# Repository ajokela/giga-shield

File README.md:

# Arduino Giga R1 WiFi Shield - Driven Level Shifter Redesign

## Overview

This is a redesigned shield/daughter board for the **Arduino Giga R1 WiFi** that replaces the original TXB0108PW auto-sensing bidirectional level translators with **SN74LVC8T245PW** driven (direction-controlled) level shifters.

The board provides 72 channels of 3.3V-to-5V level shifting across 9 ICs, mapping the Giga's 3.3V GPIO signals to 5V-compatible headers suitable for interfacing with retro hardware such as the Z80 CPU via a RetroShield.

## Why the Redesign

The original board used **TXB0108PW** auto-sensing bidirectional level translators. While convenient (no direction pin needed), the auto-sensing mechanism fails during Z80 bus cycles when signals are tri-stated. During these periods, the TXB0108 cannot determine the correct drive direction, causing the Arduino to be completely blind to certain Z80 execution states. This makes reliable bus monitoring and intervention impossible.

The **SN74LVC8T245PW** is a driven (explicit direction control) 8-bit dual-supply bus transceiver. The DIR pin explicitly sets the translation direction:
- **DIR LOW** = A-port to B-port (3.3V to 5V)
- **DIR HIGH** = B-port to A-port (5V to 3.3V)

This eliminates the ambiguity during tri-state periods and gives the Arduino full control over when it's reading vs. writing the bus.

## Board Specifications

| Parameter | Value |
|-----------|-------|
| Dimensions | 155mm x 90mm |
| Layers | 2 (top + bottom copper) |
| Level Shifters | 9x SN74LVC8T245PW (TSSOP-24) |
| Decoupling Caps | 27x 0.1uF ceramic (0603) |
| DIR Pull-downs | 9x 10K resistor (0603) |
| Connectors | 10x pin headers (J1-J10) + 1x DIR control (J11) |
| Mounting Holes | 4x 3.2mm |
| Traces | 1843 |
| Vias | 158 |

## Signal Mapping

Each SN74LVC8T245PW translates 8 signals between the Giga's 3.3V domain (A-port) and the 5V headers (B-port).

### U1 - SCL/SDA/D9-D13
| A-Port (3.3V) | B-Port (5V) | Function |
|----------------|-------------|----------|
| SCL1 | PB6 | I2C Clock |
| SDA1 | PH12 | I2C Data |
| AREF_3V3 | AREF | Analog Reference |
| D13 | PH6 | Digital 13 |
| D12 | PJ11 | Digital 12 |
| D11 | PJ10 | Digital 11 |
| D10 | PK1 | Digital 10 |
| D9 | PB9 | Digital 9 |

### U2 - Analog A0-A7
| A-Port (3.3V) | B-Port (5V) | Function |
|----------------|-------------|----------|
| PC4 | A0 | Analog 0 |
| PC5 | A1 | Analog 1 |
| PB0 | A2 | Analog 2 |
| PB1 | A3 | Analog 3 |
| PC3 | A4 | Analog 4 |
| PC2 | A5 | Analog 5 |
| PC0 | A6 | Analog 6 |
| PA0 | A7 | Analog 7 |

### U3 - Digital D1-D8
| A-Port (3.3V) | B-Port (5V) | Function |
|----------------|-------------|----------|
| D8 | PB8 | Digital 8 |
| D7 | PB4 | Digital 7 |
| D6 | PD13_5V | Digital 6 |
| D5 | PA7 | Digital 5 |
| D4 | PJ8 | Digital 4 |
| D3 | PA2 | Digital 3 |
| D2 | PA3 | Digital 2 |
| D1 | PA9 | Digital 1 |

### U4 - Analog A8-A11, DAC, CAN
| A-Port (3.3V) | B-Port (5V) | Function |
|----------------|-------------|----------|
| PC2_C | A8 | Analog 8 |
| PC3_C | A9 | Analog 9 |
| PA1_C | A10 | Analog 10 |
| PA0_C | A11 | Analog 11 |
| PA4 | DAC0 | DAC Channel 0 |
| PA5 | DAC1 | DAC Channel 1 |
| PB5 | CAN_RX | CAN Bus RX |
| PB13 | CAN_TX | CAN Bus TX |

### U5 - Digital D0, D14-D20
| A-Port (3.3V) | B-Port (5V) | Function |
|----------------|-------------|----------|
| D0 | PB7 | Digital 0 |
| D14 | PG14 | Digital 14 |
| D15 | PC7 | Digital 15 |
| D16 | PH13 | Digital 16 |
| D17 | PI9 | Digital 17 |
| D18 | PD5 | Digital 18 |
| D19 | PD6 | Digital 19 |
| D20 | PB11 | Digital 20 |

### U6 - Digital Even D22-D36
| A-Port (3.3V) | B-Port (5V) | Function |
|----------------|-------------|----------|
| D22 | PJ12 | Digital 22 |
| D24 | PG12 | Digital 24 |
| D26 | PJ14 | Digital 26 |
| D28 | PJ15 | Digital 28 |
| D30 | PK3 | Digital 30 |
| D32 | PK4 | Digital 32 |
| D34 | PK5 | Digital 34 |
| D36 | PK6 | Digital 36 |

### U7 - Digital Odd D37-D51
| A-Port (3.3V) | B-Port (5V) | Function |
|----------------|-------------|----------|
| D37 | PJ6 | Digital 37 |
| D39 | PI14 | Digital 39 |
| D41 | PK7 | Digital 41 |
| D43 | PI10 | Digital 43 |
| D45 | PI13 | Digital 45 |
| D47 | PB2 | Digital 47 |
| D49 | PE4 | Digital 49 |
| D51 | PE5 | Digital 51 |

### U8 - Digital Odd D21-D35
| A-Port (3.3V) | B-Port (5V) | Function |
|----------------|-------------|----------|
| D21 | PH4 | Digital 21 |
| D23 | PG13 | Digital 23 |
| D25 | PJ0 | Digital 25 |
| D27 | PJ1 | Digital 27 |
| D29 | PJ2 | Digital 29 |
| D31 | PJ3 | Digital 31 |
| D33 | PJ4 | Digital 33 |
| D35 | PJ5 | Digital 35 |

### U9 - Digital Even D38-D52
| A-Port (3.3V) | B-Port (5V) | Function |
|----------------|-------------|----------|
| D38 | PJ7 | Digital 38 |
| D40 | PE6 | Digital 40 |
| D42 | PI15 | Digital 42 |
| D44 | PG10 | Digital 44 |
| D46 | PH15 | Digital 46 |
| D48 | PK0 | Digital 48 |
| D50 | PI11 | Digital 50 |
| D52 | PK2 | Digital 52 |

## DIR Control (J11)

The J11 header provides per-shifter direction control. Each pin corresponds to one SN74LVC8T245PW's DIR input. A **10K pull-down resistor** on each DIR line defaults the direction to **A-to-B (3.3V to 5V)**.

| J11 Pin | Signal | Controls |
|---------|--------|----------|
| 1 | DIR_U1 | U1 (SCL/SDA/D9-D13) |
| 2 | DIR_U2 | U2 (A0-A7) |
| 3 | DIR_U3 | U3 (D1-D8) |
| 4 | DIR_U4 | U4 (A8-A11/DAC/CAN) |
| 5 | DIR_U5 | U5 (D0/D14-D20) |
| 6 | DIR_U6 | U6 (Even D22-D36) |
| 7 | DIR_U7 | U7 (Odd D37-D51) |
| 8 | DIR_U8 | U8 (Odd D21-D35) |
| 9 | DIR_U9 | U9 (Even D38-D52) |
| 10 | GND | Ground reference |

To change a shifter's direction to **B-to-A (5V to 3.3V)**, drive the corresponding J11 pin HIGH (3.3V). This is done by running jumper wires from available Giga GPIO pins to the J11 header. Software then controls direction by toggling those GPIOs.

## Connectors

| Ref | Type | Pins | Location | Function |
|-----|------|------|----------|----------|
| J1 | 1x8 | 8 | Bottom edge | Giga 3.3V analog header |
| J2 | 1x10 | 10 | Top edge | Giga 3.3V header (power/analog ext) |
| J3 | 1x8 | 8 | Bottom edge | Giga 3.3V digital D1-D8 |
| J4 | 1x8 | 8 | Top edge | Giga 3.3V digital SCL/SDA/D9-D13 |
| J5 | 1x26 | 26 | Bottom edge | 5V analog header (J_ANALOG) |
| J6 | 1x8 | 8 | Bottom edge | Giga 3.3V digital D0/D14-D20 |
| J7 | 1x8 | 8 | Top edge | Giga 3.3V D21 + misc |
| J8 | 1x26 | 26 | Top edge | 5V digital header (J_DIGITAL) |
| J9 | 2x18 | 36 | Right side | 3.3V side connector (JSIDE) |
| J10 | 2x18 | 36 | Right side | 5V side connector (JSIDE_5V) |
| J11 | 1x10 | 10 | Center-left | DIR control header |

## Design Toolchain

The original board was designed in **KiCad 9.0** (file version 20241229). Since pcb-rnd 3.1.4 cannot read KiCad 9.0 files (version too new), the board was rebuilt from scratch using a Python generator script.

### Tools Used

| Tool | Version | Purpose |
|------|---------|---------|
| KiCad | 9.0.6 | Original design source, position/netlist reference |
| pcb-rnd | 3.1.4 | PCB format, DSN export, gerber/PNG export |
| Freerouting | 1.9.0 | Specctra-based autorouter |
| Python | 3.x | Board generator script (`build_giga_shield.py`) |

### Build Pipeline

1. **`build_giga_shield.py`** generates `giga_shield.pcb` with all components placed, footprints defined, and netlist specified in pcb-rnd native format
2. **pcb-rnd** exports the unrouted board to Specctra DSN format (`giga_shield.dsn`)
3. **Freerouting** reads the DSN, autoroutes all nets, and outputs a Specctra session file (`giga_shield.ses`)
4. **`ses_to_pcb.py`** imports the routed traces from the SES file back into the PCB
5. **pcb-rnd** exports final gerbers, drill files, and photo-realistic PNG renderings

### Key Implementation Details

- Component positions were extracted from the original KiCad PCB and translated from KiCad's coordinate origin (x=106mm, y=30.5mm) to pcb-rnd's (0,0) origin using the `kpos()` function
- All 1x pin headers are rotated 90 degrees to run horizontally along the board edges, matching the original KiCad layout (the Arduino Giga shield form factor has edge-parallel headers)
- TSSOP-24 footprints are generated programmatically with correct 0.65mm pitch, 6.4mm pad-to-pad span
- The SN74LVC8T245PW pin mapping was carefully verified against the datasheet: pins 1-12 on the left (DIR, A1-A4, GND, A5-A8, OE#, GND) and pins 13-24 on the right (B8-B5, VCCB, B4-B1, VCCA, VCCA, VCCB)
- OE# (pin 11) is tied to GND on all shifters (always enabled)
- Each shifter has two 0.1uF decoupling caps: one on VCCA (3.3V) and one on VCCB (5V)
- An additional 9 decoupling caps are placed along the bottom edge for power rail filtering

## SN74LVC8T245PW vs TXB0108PW

| Feature | TXB0108PW (Original) | SN74LVC8T245PW (New) |
|---------|----------------------|----------------------|
| Package | TSSOP-20 | TSSOP-24 |
| Channels | 8 | 8 |
| Direction | Auto-sensing | Explicit DIR pin |
| A-Port Voltage | 1.2V - 3.6V | 1.2V - 3.6V |
| B-Port Voltage | 1.65V - 5.5V | 1.65V - 5.5V |
| Max Data Rate | 100 Mbps | 380 Mbps |
| Tri-state Handling | Unreliable | Deterministic |
| Output Enable | OE (active low) | OE# (active low) |
| Extra Pins | None | DIR control |

## Files

| File | Description |
|------|-------------|
| `build_giga_shield.py` | Python script that generates the entire PCB from scratch |
| `giga_shield.pcb` | Final routed PCB in pcb-rnd format |
| `giga_shield.dsn` | Specctra DSN export for autorouting |
| `giga_shield.ses` | Specctra session file with routing solution |
| `giga_shield_bom.csv` | Bill of materials |
| `giga_shield_centroid.csv` | Pick-and-place centroid file (SMD components) |
| `giga_shield_gerbers.zip` | Production files (gerbers + BOM + centroid) |
| `giga_shield_top.png` | Photo-realistic top view rendering |
| `giga_shield_bottom.png` | Photo-realistic bottom view rendering |
| `sn74lvc8t245_pinout.txt` | SN74LVC8T245 pinout reference |
| `kicad_source/` | Original KiCad 9.0 design files (reference) |
| `kicad_source/AlexJ_bz_ArduinoGigaShield.kicad_pcb` | Original KiCad PCB |
| `kicad_source/AlexJ_bz_ArduinoGigaShield.kicad_sch` | Original KiCad schematic |
| `kicad_source/AlexJ_bz_ArduinoGigaShield.pdf` | Original schematic PDF |
| `kicad_source/giga_pos.csv` | Component positions exported from KiCad |
| `kicad_source/giga_netlist.d356` | IPC-D-356 netlist exported from KiCad |

## Board Renderings

### Top

### Bottom

## Development Notes

This section documents the full development process, including toolchain issues, format debugging, and workarounds encountered during the redesign.

### Starting Point

The original design (`AlexJ_bz_ArduinoGigaShield.kicad_pcb`) was created in **KiCad 9.0** (internal file version 20241229) with 9x TXB0108PW auto-sensing level shifters. The goal was to convert this to pcb-rnd format, swap in SN74LVC8T245PW driven shifters, and produce a fully routed production board.

### KiCad 9.0 to pcb-rnd Conversion Failure

pcb-rnd 3.1.4 includes an `io_kicad` plugin for reading KiCad files, but it only supports older KiCad versions. Attempting to open the KiCad 9.0 PCB produced:

```
unexpected layout version number (perhaps too new)
```

This was a hard blocker — there is no format converter from KiCad 9.0 to pcb-rnd.

### Extracting Data from KiCad

Since direct conversion was impossible, component positions and netlist data were extracted from KiCad using available tools:

1. **Component positions** were exported using `kicad-cli`:
   ```
   kicad-cli pcb export pos AlexJ_bz_ArduinoGigaShield.kicad_pcb -o giga_pos.csv
   ```

2. **Netlist/connectivity** was exported via IPC-D-356:
   ```
   kicad-cli pcb export ipc2581 ... -o giga_netlist.d356
   ```

3. **Signal mappings** (which Giga pin connects to which 5V header pin through which shifter) were extracted by parsing the KiCad schematic file (`AlexJ_bz_ArduinoGigaShield.kicad_sch`), which uses an s-expression format with positional net connections across hierarchical sheets.

### Building the Board from Scratch

With positions and netlist in hand, `build_giga_shield.py` was written to generate the entire pcb-rnd board programmatically. This script:

- Converts KiCad coordinates to pcb-rnd coordinates (KiCad origin at x=106mm, y=30.5mm; pcb-rnd at 0,0) using:
  ```python
  KX, KY = 106.0, 30.5
  def kpos(kx, ky):
      return (mm(kx - KX), mm(ky - KY))
  ```
- Generates TSSOP-24 footprints for the SN74LVC8T245PW (0.65mm pitch, 6.4mm pad-to-pad span, 24 pins with correct pin naming)
- Creates 0603 SMD footprints for decoupling caps and pull-down resistors
- Creates through-hole pin header footprints with rotation support
- Builds the complete netlist mapping all 72 signal channels across 9 shifters
- Outputs a valid pcb-rnd `.pcb` file

### pcb-rnd Format Debugging

Getting pcb-rnd to accept the generated file required solving several format issues. pcb-rnd's parser error messages were often unhelpful — errors in element definitions would sometimes be reported at a much later line (e.g., the outline layer starting at line 959).

**Issue 1: Element `"smd"` flag**

```
Element["smd" "TSSOP24" "U1" ...]
```
pcb-rnd rejected this with `Unknown flag: smd ignored`, which cascaded into a parse failure. The fix was to use an empty string for the first field:
```
Element["" "TSSOP24" "U1" ...]
```

**Issue 2: Bare `0` without unit suffix**

Mixed use of `0` and `0nm` in coordinate values caused silent parse errors:
```
Pin[0 0 1700000nm ...]    # WRONG - bare 0
Pin[0nm 0nm 1700000nm ...]  # CORRECT
```
All zero values needed the explicit `nm` suffix for consistency.

**Issue 3: Layer `Line[]` missing flags argument**

The `Line[]` entry inside Layer blocks requires 7 fields, but the generator was only outputting 6 (omitting the flags string):
```
Line[x1 y1 x2 y2 thickness clearance]           # WRONG - 6 fields
Line[x1 y1 x2 y2 thickness clearance "clearline"]  # CORRECT - 7 fields
```
The error was `syntax error, unexpected ']', expecting INTEGER or STRING`, which appeared at the outline layer rather than at the actual problematic line.

**Debugging technique: Binary search with file truncation**

Since pcb-rnd always reported the error at the same line regardless of where the actual issue was, a binary search approach was used — progressively truncating the file with `head -N` to isolate which section introduced the parse failure:
```
head -100 giga_shield.pcb > test.pcb && pcb-rnd -x png test.pcb  # OK → mounting holes fine
head -300 giga_shield.pcb > test.pcb && pcb-rnd -x png test.pcb  # OK → connectors fine
head -500 giga_shield.pcb > test.pcb && pcb-rnd -x png test.pcb  # OK → shifters fine
head -700 giga_shield.pcb > test.pcb && pcb-rnd -x png test.pcb  # OK → all elements fine
head -960 giga_shield.pcb > test.pcb && pcb-rnd -x png test.pcb  # FAIL → layers are the problem
```
This narrowed the issue to the Layer blocks, where the missing flags argument was found.

### Connector Rotation

The initial build placed all pin headers with pins extending downward (+Y). For the Arduino Giga shield form factor, the long 1x headers actually run horizontally along the board edges. Without rotation, J5 (1x26 at y=84mm) extended 63.5mm downward to y=148mm — well past the 90mm board edge. J11 (1x10 at y=75mm) similarly extended to y=98mm.

The fix involved:
1. Extracting rotation angles from the original KiCad PCB — all 1x headers had 90° or -90° rotation
2. Adding a `rot` parameter to `pin_header_element()` with a rotation transform:
   ```python
   def rotate(px, py):
       if rot == 90:     # KiCad 90° → pins extend in +X
           return (py, -px)
       elif rot == -90:  # KiCad -90° → pins extend in -X
           return (-py, px)
       return (px, py)
   ```
3. Applying rotation to both pin coordinates and element outlines

After rotation, all connectors fit within the board:
- J5 (1x26): x=[40.6, 104.1], y=84.2 — runs along the bottom edge
- J8 (1x26): x=[39.0, 102.5], y=6.8 — runs along the top edge
- J11 (1x10): x=[40.0, 62.9], y=75.0 — runs horizontally on the board

### Remote Toolchain

pcb-rnd is not readily available on macOS. All pcb-rnd operations (DSN export, gerber generation, PNG rendering) were performed on a remote Linux machine via SSH:

```bash
# Upload PCB
scp giga_shield.pcb alex@192.168.0.219:/tmp/

# Export DSN for autorouting
ssh alex@192.168.0.219 'cd /tmp && pcb-rnd -x dsn giga_shield.pcb'

# Export gerbers
ssh alex@192.168.0.219 'cd /tmp && pcb-rnd -x gerber giga_shield.pcb'

# Render photo-realistic PNG (600 DPI, green solder mask, gold plating)
ssh alex@192.168.0.219 'pcb-rnd -x png --dpi 600 --photo-mode --outfile top.png giga_shield.pcb'
ssh alex@192.168.0.219 'pcb-rnd -x png --dpi 600 --photo-mode --photo-flip-y --outfile bottom.png giga_shield.pcb'

# Download results
scp alex@192.168.0.219:/tmp/giga_shield.*.gbr .
scp alex@192.168.0.219:/tmp/top.png giga_shield_top.png
```

### Autorouting Pipeline

The routing pipeline uses Specctra DSN/SES interchange format as the bridge between pcb-rnd and Freerouting:

```
giga_shield.pcb → [pcb-rnd DSN export] → giga_shield.dsn
                                               ↓
                                    [Freerouting autorouter]
                                         (~55 minutes)
                                               ↓
giga_shield.pcb ← [ses_to_pcb.py]  ← giga_shield.ses
```

**Freerouting** (v1.9.0) is a Java-based Specctra autorouter:
```bash
java -jar freerouting-1.9.0.jar -de giga_shield.dsn -do giga_shield.ses -mp 60
```
The `-mp 60` flag sets 60 optimization passes. A typical run takes ~55 minutes and produces optimized routing with ~1843 traces and ~158 vias.

**`ses_to_pcb.py`** parses the Freerouting SES output and injects `Line[]` entries (traces) and `Via[]` entries into the pcb-rnd PCB file's Layer blocks.

**`strip_traces.py`** removes all routed traces and autorouted vias from a PCB file, leaving only components and netlist — used to prepare for re-routing after component moves. It identifies autorouted vias by their 914400nm pad size (the default from `ses_to_pcb.py`).

Both helper scripts originate from the [dual-z80](https://github.com/ajokela/dual-z80) project.

### Reproduction Steps

To rebuild the board from scratch:

```bash
# 1. Generate the unrouted PCB
python3 build_giga_shield.py giga_shield.pcb

# 2. Export DSN (on a machine with pcb-rnd installed)
pcb-rnd -x dsn giga_shield.pcb

# 3. Run Freerouting (~55 minutes)
java -jar freerouting-1.9.0.jar -de giga_shield.dsn -do giga_shield.ses -mp 60

# 4. Import routes back into PCB
python3 ses_to_pcb.py giga_shield.ses giga_shield.pcb

# 5. Export gerbers
pcb-rnd -x gerber giga_shield.pcb

# 6. Render board images
pcb-rnd -x png --dpi 600 --photo-mode --outfile giga_shield_top.png giga_shield.pcb
pcb-rnd -x png --dpi 600 --photo-mode --photo-flip-y --outfile giga_shield_bottom.png giga_shield.pcb
```

To re-route after component changes:
```bash
# Strip existing traces
python3 strip_traces.py giga_shield.pcb

# Then repeat steps 2-6 above
```

## License

BSD 3-Clause License

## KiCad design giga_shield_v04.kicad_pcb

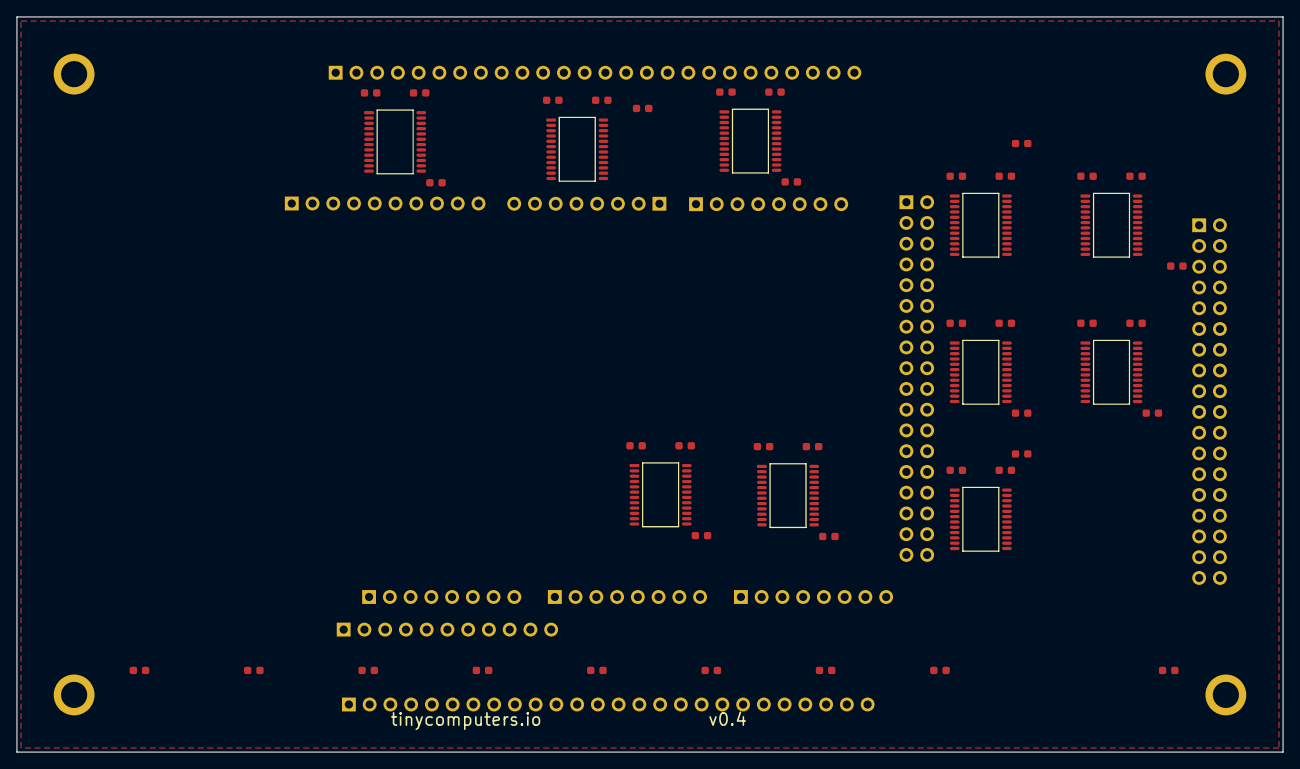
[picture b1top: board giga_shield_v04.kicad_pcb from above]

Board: 2 copper layers, 155.0 x 90.0 mm, 64 parts (0 on the bottom side), 161 nets, no tracks yet.

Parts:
C1, C2, C3, C4, C5, C6, C7, C8, C9, C10, C11, C12, C13, C14, C15, C16, C17, C18, C19, C20, C21, C22, C23, C24, C25, C26, C27, C28, C29: 0.1uF; R_0603_1608Metric
H1, H2, H3, H4: MountingHole; MountingHole_3.2mm_M3
J1, J3, J4, J6, J7: Conn_01x08; Connector_PinHeader_1x08_P2.54mm_Vertical
J2: Conn_01x10; Connector_PinHeader_1x10_P2.54mm_Vertical
J5: J_ANALOG; Connector_PinHeader_1x26_P2.54mm_Vertical
J8: J_DIGITAL; Connector_PinHeader_1x26_P2.54mm_Vertical
J9: JSIDE; Connector_PinHeader_2x18_P2.54mm_Vertical
J10: JSIDE_5V; Connector_PinHeader_2x18_P2.54mm_Vertical
J11: DIR_CTRL; Connector_PinHeader_1x11_P2.54mm_Vertical
R1, R2, R3, R4, R5, R6, R7, R8, R9, R10: 10K; R_0603_1608Metric
U1, U2, U3, U4, U5, U6, U7, U8, U9, U10: SN74LVC8T245PW; TSSOP-24_4.4x7.8mm_P0.65mm

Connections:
+3V3: C1.1, C3.1, C5.1, C7.1, C9.1, C11.1, C13.1, C15.1, C17.1, C19.1, C21.1, C23.1, C25.1, C27.1, C29.1, J2.2, J2.3, J5.4, J7.5, R10.2, U1.22, U1.23, U2.22, U2.23, U3.22, U3.23, U4.22, U4.23, U5.22, U5.23, U6.22, U6.23, U7.22, U7.23, U8.22, U8.23, U9.22, U9.23, U10.22, U10.23
+5V: C2.1, C4.1, C6.1, C8.1, C10.1, C12.1, C14.1, C16.1, C18.1, C20.1, C22.1, C24.1, C26.1, C28.1, J5.5, J7.7, J9.1, J9.2, J10.1, J10.2, U1.17, U1.24, U2.17, U2.24, U3.17, U3.24, U4.17, U4.24, U5.17, U5.24, U6.17, U6.24, U7.17, U7.24, U8.17, U8.24, U9.17, U9.24, U10.17, U10.24
A0: J5.9, U2.21
A1: J5.10, U2.20
A2: J5.11, U2.19
A3: J5.12, U2.18
A4: J5.13, U2.16
A5: J5.14, U2.15
A6: J5.15, U2.14
A7: J5.16, U2.13
A8: J5.17, U4.21
A9: J5.18, U4.20
A10: J5.19, U4.19
A11: J5.20, U4.18
AREF: J8.3, U1.19
AREF_3V3: J4.3, U1.4
CAN_RX: J5.23, U4.14
CAN_TX: J5.24, U4.13
D0: J6.1, U5.2
D1: J3.8, U3.10
D2: J3.7, U3.9
D3: J3.6, U3.8
D4: J3.5, U3.7
D5: J3.4, U3.5
D6: J3.3, U3.4
D7: J3.2, U3.3
D8: J3.1, U3.2
D9: J4.8, U1.10
D10: J4.7, U1.9
D11: J4.6, U1.8
D12: J4.5, U1.7
D13: J4.4, U1.5
D14: J6.2, U5.3
D15: J6.3, U5.4
D16: J6.4, U5.5
D17: J6.5, U5.7
D18: J6.6, U5.8
D19: J6.7, U5.9
D20: J6.8, U5.10
D21: J7.1, U8.2
D22: J9.3, U6.2
D23: J9.4, U8.3
D24: J9.5, U6.3
D25: J9.6, U8.4
D26: J9.7, U6.4
D27: J9.8, U8.5
D28: J9.9, U6.5
D29: J9.10, U8.7
D30: J9.11, U6.7
D31: J9.12, U8.8
D32: J9.13, U6.8
D33: J9.14, U8.9
D34: J9.15, U6.9
D35: J9.16, U8.10
D36: J9.17, U6.10
D37: J9.18, U9.2
D38: J9.19, U10.2
D39: J9.20, U9.3
D40: J9.21, U9.4
D41: J9.22, U9.5
D42: J9.23, U7.2
D43: J9.24, U7.3
D44: J9.25, U7.4
D45: J9.26, U7.5
D46: J9.27, U7.7
D47: J9.28, U7.8
D48: J9.29, U7.9
D49: J9.30, U7.10
D50: J9.31, U10.3
D51: J9.32, U10.4
D52: J9.33, U10.5
D53: J9.34, U9.7
DAC0: J5.21, U4.16
DAC1: J5.22, U4.15
DIR_U1: J11.1, R1.1, U1.1
DIR_U2: J11.2, R2.1, U2.1
DIR_U3: J11.3, R3.1, U3.1
DIR_U4: J11.4, R4.1, U4.1
DIR_U5: J11.5, R5.1, U5.1
DIR_U6: J11.6, R6.1, U6.1
DIR_U7: J11.7, R7.1, U7.1
DIR_U8: J11.8, R8.1, U8.1
DIR_U9: J11.9, R9.1, U9.1
DIR_U10: J11.10, R10.1, U10.1
GND: C1.2, C2.2, C3.2, C4.2, C5.2, C6.2, C7.2, C8.2, C9.2, C10.2, C11.2, C12.2, C13.2, C14.2, C15.2, C16.2, C17.2, C18.2, C19.2, C20.2, C21.2, C22.2, C23.2, C24.2, C25.2, C26.2, C27.2, C28.2, C29.2, J5.6, J5.7, J7.6, J7.8, J8.4, J9.35, J9.36, J10.35, J10.36, J11.11, R1.2, R2.2, R3.2, R4.2, R5.2, R6.2, R7.2, R8.2, R9.2, U1.6, U1.11, U1.12, U2.6, U2.11, U2.12, U3.6, U3.11, U3.12, U4.6, U4.11, U4.12, U5.6, U5.11, U5.12, U6.6, U6.11, U6.12, U7.6, U7.11, U7.12, U8.6, U8.11, U8.12, U9.6, U9.11, U9.12, U10.6, U10.11, U10.12
IOREF_3V3: J2.4, J5.2
NRST: J2.5, J5.3
PA0: J1.8, U2.10
PA0_C: J2.9, U4.5
PA1_C: J2.8, U4.4
PA2: J8.15, U3.15
PA3: J8.16, U3.14
PA4: J7.2, U4.7
PA5: J7.3, U4.8
PA7: J8.13, U3.18
PA9: J8.17, U3.13
PB0: J1.3, U2.4
PB1: J1.4, U2.5
PB2: J10.28, U7.15
PB4: J8.11, U3.20
PB5: J7.4, U4.9
PB6: J8.1, U1.21
PB7: J8.18, U5.21
PB8: J8.10, U3.21
PB9: J8.9, U1.13
PB11: J8.25, U5.13
PB13: J2.10, U4.10
PC0: J1.7, U2.9
PC2: J1.6, U2.8
PC2_C: J2.6, U4.2
PC3: J1.5, U2.7
PC3_C: J2.7, U4.3
PC4: J1.1, U2.2
PC5: J1.2, U2.3
PC7: J8.20, U5.19
PD5: J8.23, U5.15
PD6: J8.24, U5.14
PD13_5V: J8.12, U3.19
PE4: J10.30, U7.13
PE5: J10.32, U10.19
PE6: J10.21, U9.19
PG7: J10.34, U9.16
PG10: J10.25, U7.19
PG12: J10.5, U6.20
PG13: J10.4, U8.20
PG14: J8.19, U5.20
PH4: J8.26, U8.21
PH6: J8.5, U1.18
PH12: J8.2, U1.20
PH13: J8.21, U5.18
PH15: J10.27, U7.16
PI9: J8.22, U5.16
PI10: J10.24, U7.20
PI11: J10.31, U10.20
PI13: J10.26, U7.18
PI14: J10.20, U9.20
PI15: J10.23, U7.21
PJ0: J10.6, U8.19
PJ1: J10.8, U8.18
PJ2: J10.10, U8.16
PJ3: J10.12, U8.15
PJ4: J10.14, U8.14
PJ5: J10.16, U8.13
PJ6: J10.18, U9.21
PJ7: J10.19, U10.21
PJ8: J8.14, U3.16
PJ10: J8.7, U1.15
PJ11: J8.6, U1.16
PJ12: J10.3, U6.21
PJ14: J10.7, U6.19
PJ15: J10.9, U6.18
PK0: J10.29, U7.14
PK1: J8.8, U1.14
PK2: J10.33, U10.18
PK3: J10.11, U6.16
PK4: J10.13, U6.15
PK5: J10.15, U6.14
PK6: J10.17, U6.13
PK7: J10.22, U9.18
SCL1: J4.1, U1.2
SDA1: J4.2, U1.3

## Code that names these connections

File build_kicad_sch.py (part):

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SHIFTER_NETS = {
    'U1': {
        'a': ['SCL1', 'SDA1', 'AREF_3V3', 'D13', 'D12', 'D11', 'D10', 'D9'],
        'b': ['PB6', 'PH12', 'AREF', 'PH6', 'PJ11', 'PJ10', 'PK1', 'PB9'],
        'dir_net': 'DIR_U1',
    },
    'U2': {
        'a': ['PC4', 'PC5', 'PB0', 'PB1', 'PC3', 'PC2', 'PC0', 'PA0'],
        'b': ['A0', 'A1', 'A2', 'A3', 'A4', 'A5', 'A6', 'A7'],
        'dir_net': 'DIR_U2',
    },
    'U3': {
        'a': ['D8', 'D7', 'D6', 'D5', 'D4', 'D3', 'D2', 'D1'],
        'b': ['PB8', 'PB4', 'PD13_5V', 'PA7', 'PJ8', 'PA2', 'PA3', 'PA9'],
        'dir_net': 'DIR_U3',
    },
    'U4': {
        'a': ['PC2_C', 'PC3_C', 'PA1_C', 'PA0_C', 'PA4', 'PA5', 'PB5', 'PB13'],
        'b': ['A8', 'A9', 'A10', 'A11', 'DAC0', 'DAC1', 'CAN_RX', 'CAN_TX'],
        'dir_net': 'DIR_U4',
    },
    'U5': {
        'a': ['D0', 'D14', 'D15', 'D16', 'D17', 'D18', 'D19', 'D20'],
        'b': ['PB7', 'PG14', 'PC7', 'PH13', 'PI9', 'PD5', 'PD6', 'PB11'],
        'dir_net': 'DIR_U5',
    },
    'U6': {
        'a': ['D22', 'D24', 'D26', 'D28', 'D30', 'D32', 'D34', 'D36'],
        'b': ['PJ12', 'PG12', 'PJ14', 'PJ15', 'PK3', 'PK4', 'PK5', 'PK6'],
        'dir_net': 'DIR_U6',
    },
    'U7': {
        'a': ['D42', 'D43', 'D44', 'D45', 'D46', 'D47', 'D48', 'D49'],
        'b': ['PI15', 'PI10', 'PG10', 'PI13', 'PH15', 'PB2', 'PK0', 'PE4'],
        'dir_net': 'DIR_U7',
    },
    'U8': {
        'a': ['D21', 'D23', 'D25', 'D27', 'D29', 'D31', 'D33', 'D35'],
        'b': ['PH4', 'PG13', 'PJ0', 'PJ1', 'PJ2', 'PJ3', 'PJ4', 'PJ5'],
        'dir_net': 'DIR_U8',
    },
    'U9': {
        'a': ['D37', 'D39', 'D40', 'D41', 'D53', 'NC_U9A6', 'NC_U9A7', 'NC_U9A8'],
        'b': ['PJ6', 'PI14', 'PE6', 'PK7', 'PG7', 'NC_U9B6', 'NC_U9B7', 'NC_U9B8'],
        'dir_net': 'DIR_U9',
    },
    'U10': {
        'a': ['D38', 'D50', 'D51', 'D52', 'NC_U10A5', 'NC_U10A6', 'NC_U10A7', 'NC_U10A8'],
        'b': ['PJ7', 'PI11', 'PE5', 'PK2', 'NC_U10B5', 'NC_U10B6', 'NC_U10B7', 'NC_U10B8'],
        'dir_net': 'DIR_U10',
    },
}

# Connector pin lists
CONNECTORS = {
    'J1':  {'pins': ['PC4', 'PC5', 'PB0', 'PB1', 'PC3', 'PC2', 'PC0', 'PA0'], 'val': '1x08 Analog 3.3V'},
    'J2':  {'pins': ['VIN', '+3V3', '+3V3', 'IOREF_3V3', 'NRST', 'PC2_C', 'PC3_C', 'PA1_C', 'PA0_C', 'PB13'], 'val': '1x10 Power 3.3V'},
    'J3':  {'pins': ['D8', 'D7', 'D6', 'D5', 'D4', 'D3', 'D2', 'D1'], 'val': '1x08 Digital 3.3V'},
    'J4':  {'pins': ['SCL1', 'SDA1', 'AREF_3V3', 'D13', 'D12', 'D11', 'D10', 'D9'], 'val': '1x08 Digital 3.3V'},
    'J5':  {'pins': ['NC', 'IOREF_3V3', 'NRST', '+3V3', '+5V', 'GND', 'GND', 'VIN',
                     'A0', 'A1', 'A2', 'A3', 'A4', 'A5', 'A6', 'A7',
                     'A8', 'A9', 'A10', 'A11', 'DAC0', 'DAC1', 'CAN_RX', 'CAN_TX', 'NC', 'NC'], 'val': '1x26 Analog 5V'},
    'J6':  {'pins': ['D0', 'D14', 'D15', 'D16', 'D17', 'D18', 'D19', 'D20'], 'val': '1x08 Digital 3.3V'},
    'J7':  {'pins': ['D21', 'PA4', 'PA5', 'PB5', '+3V3', 'GND', '+5V', 'GND'], 'val': '1x08 Misc 3.3V'},
    'J8':  {'pins': ['PB6', 'PH12', 'AREF', 'GND',
                     'PH6', 'PJ11', 'PJ10', 'PK1', 'PB9',
                     'PB8', 'PB4', 'PD13_5V', 'PA7', 'PJ8', 'PA2', 'PA3', 'PA9',
                     'PB7', 'PG14', 'PC7', 'PH13', 'PI9', 'PD5', 'PD6', 'PB11', 'PH4'], 'val': '1x26 Digital 5V'},
    'J9':  {'pins': ['+5V', '+5V',
                     'D22', 'D23', 'D24', 'D25', 'D26', 'D27', 'D28', 'D29',
                     'D30', 'D31', 'D32', 'D33', 'D34', 'D35', 'D36', 'D37',
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                     'D46', 'D47', 'D48', 'D49', 'D50', 'D51', 'D52', 'D53',
                     'GND', 'GND'], 'val': '2x18 Side 3.3V'},
    'J10': {'pins': ['+5V', '+5V',
                     'PJ12', 'PG13', 'PG12', 'PJ0', 'PJ14', 'PJ1', 'PJ15', 'PJ2',
                     'PK3', 'PJ3', 'PK4', 'PJ4', 'PK5', 'PJ5', 'PK6', 'PJ6',
                     'PJ7', 'PI14', 'PE6', 'PK7', 'PI15', 'PI10', 'PG10', 'PI13',
                     'PH15', 'PB2', 'PK0', 'PE4', 'PI11', 'PE5', 'PK2', 'PG7',
                     'GND', 'GND'], 'val': '2x18 Side 5V'},
    'J11': {'pins': ['DIR_U1', 'DIR_U2', 'DIR_U3', 'DIR_U4', 'DIR_U5',
                     'DIR_U6', 'DIR_U7', 'DIR_U8', 'DIR_U9', 'DIR_U10', 'GND'], 'val': '1x11 DIR Control'},
}

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
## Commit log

2026-03-08 Initial commit: Arduino Giga R1 Shield with SN74LVC8T245PW driven level shifters
    Redesigned from original TXB0108PW auto-sensing design to fix Z80 bus
    tri-state blindness. 9x SN74LVC8T245PW, 155x90mm 2-layer board, fully
    routed with 1843 traces/158 vias. Includes build script, gerbers, BOM,
    centroid, and original KiCad source files for reference.
2026-03-08 Move original KiCad source files into kicad_source/ subdirectory
2026-03-08 Remove loose gerber files from tracking, already in production zip
2026-03-08 Add silkscreen labels for J11 DIR control header pins
    Labels each pin (U1-U9, GND) with rotated text below the header,
    plus a "J11 DIR" title above. Includes full pcb-rnd symbol table
    for text rendering. Regenerated gerbers and renderings.
2026-03-08 Move decoupling caps C19-C27 to clear J5 overlap, add routing video
    Moved extra power decoupling caps from y=85mm to y=80mm so they no
    longer overlap with J5 (1x26 analog header at y=84.17mm). Full
    re-route: 1922 traces, 175 vias. Added routing-traces.mp4.
2026-03-08 Move R3 to clear J4 overlap, fix silk labels to Layer 5
    R3 moved from (73.6, 21.2) to (73.6, 11.2) to avoid overlapping
    J4 header pins. Silk text moved from Layer 4 to Layer 5 for proper
    rendering on top side. Re-routed: 1864 traces, 153 vias.
2026-03-08 Fix all component overlaps: R3, R6, R8 repositioned, caps respaced
    Comprehensive overlap analysis found 4 conflicts:
    - C5/R3: R3 moved further right (dx +8mm)
    - C15/R6: R6 moved above U6 (dy -10mm) to clear U8 caps
    - C17/R8: R8 moved further right (dx +8mm) to clear U9 caps
    - H2/C19: Extra decoupling caps respaced (start x=15, pitch=14mm)
    Zero overlaps verified. Re-routed: 1964 traces, 182 vias.
2026-03-08 Move J11 DIR label to the left to clear J1 header
2026-03-08 Adjust J11 DIR label position closer to header
2026-03-13 Add silkscreen branding, DSN via/rule fixes, re-routed board, drill file
    Add tinycomputers.io and v0.2 text to silkscreen in build script.
    Add via and rule definitions to DSN structure section for Freerouting.
    Updated PCB with new routing from Freerouting v1.9 (2911 traces, 172 vias).
    Regenerated gerbers, board images, and added plated drill file.
2026-04-18 Fix pin numbering bug and add KiCad build pipeline
    Fix critical zigzag pin ordering bug in pin_header_element that caused
    every signal on 2x18 headers (J9/J10) to land at wrong physical positions.
    Reposition U6-U10 in staggered layout between J9/J10 to eliminate routing
    congestion. Add build_kicad.py for KiCad PCB generation and
    build_kicad_sch.py for schematic generation. Add Arduino test sketch for
    Z80 RetroShield bus profiling. Move R10 and C29 clear of U10. Update
2026-04-20 Add v0.4 fab package, R10 pull-up fix, component repositioning
    Fix critical R10 safety issue: changed R10 from pulldown-to-GND to
    pull-up-to-+3V3 so U10 defaults to A→B direction (Giga→Z80) for
    CLK/RESET/INT/NMI. Previously would have driven 5V Z80 outputs into
    3.3V Giga inputs on power-up.
    Reposition U6-U10 in staggered two-column layout between J9/J10 for
    cleaner routing on 4 layers. Move C29 clear of U10 body.
2026-04-24 Update .gitignore to exclude build artifacts, local state, and symlinks
    Add patterns for Python venvs, __pycache__, log files, KiCad .kicad_prl
    local-state files, macOS/editor metadata, the .claude/ local tooling
    directory, the tinycomputers.io symlink to a separate project, and
    unzipped fabrication directories that are redundant with their zips.
2026-04-24 Archive v0.3 KiCad sources, gerbers, and renders
    The v0.3 design was the first Claude-assisted redesign. It shipped but
    failed bring-up due to the pin-numbering bug documented in
    'How a Pin Numbering Bug Killed a PCB'. Preserved here as the historical
    record of what was fabricated before the v0.4 respin.
2026-04-24 Add v0.4 KiCad design, routed PCB, and renders
    The v0.4 respin fixes the pin-numbering bug from v0.3 and the R10
    pull-down direction bug caught during a Claude-assisted audit. Includes
    the post-Freerouting routed kicad_pcb, the DRC report, and top-down and
    isometric renders of the board with copper pour completed.
2026-04-24 Add v0.4 routing artifacts and v0.5 intermediate design
    The v0.4.ses is the Freerouting output imported into the final routed
    board. v0.5 was an interim KiCad rework used to post-process gerbers
    when PCBWay flagged annular-ring overlap (fabrication_v05.zip). The
    KiCad-exported DSN and normalized .kicad_pro are part of the
    Freerouting feedback loop.
2026-04-24 Add fabrication packages v05 and v06 with PCBWay correspondence
    v05 fixes the first PCBWay DFM question (via annular ring overlap):
    D12/D21/D29/D51 aperture 0.0600" -> 0.0295" (1.524mm -> 0.75mm pad)
    and T11 drill 0.035" -> 0.0157" (0.889mm -> 0.4mm drill), applied as
    post-processing to the v04 gerbers.
    v06 fixes the second PCBWay DFM question (mask/paste aperture mismatch)
    at the source: 0603 cap pad mask aperture bumped from 0.6mm (smaller
2026-04-24 Add helper scripts for pours, power nets, SES import, and routing batches
    These scripts were used across the v0.4 through v0.6 pipeline:
    - add_gnd.py / add_pours.py / add_power_nets.py: inject GND, +3V3, +5V
    plane fills and power-net assignments into the KiCad PCB after initial
    generation from the Python build script
    - flip_to_bottom.py: helper for mirroring components (experimental)
    - import_ses.py: read a Freerouting .ses back into KiCad
2026-04-24 Add placement benchmark suite: pyplacer vs Quilter vs manual
    Compares three placement approaches on the v0.4 giga-shield board:
    - base/: unplaced source used as the common input to all placers
    - placement/: manual hand-placement (routes to 100% with Freerouting)
    - quilter/: Quilter.ai Candidate_1 (99.4% routed)
    - pyplacer/: open-source simulated-annealing placer (best seed ~93.8%)
    - freerouting/: the routed comparison artifacts
2026-04-24 Add ROUTING_NOTES.md: development notes on Freerouting tuning
    Captures the clearance-rule findings from the v0.4 PCBWay DFM saga (the
    121-false-positive DRC episode), the -mp/-oit/-mt Freerouting CLI flags
    that matter for reproducible runs, and the per-type clearance rule
    template that passes PCBWay's automated DFM on a 4-layer dense board.
2026-04-24 Ignore PCBWay order correspondence PDF
